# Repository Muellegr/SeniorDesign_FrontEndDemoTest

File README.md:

# SeniorDesign_FrontEndDemoTest
OSU Senior Design to demonstrate a working, very low quality front end for an oscilloscope.  
The focus of this is to test a basic fully differential op amp and applying a DC offset to the output.  
* Selectable AC or DC mode
* 5 different attenuation amounts from 1x to 20x
* Impedance matchedish to 50ohm
* Adjustable DC offset for testing from -5v to +5v
-------

Due to being used in a presentation assignment I put a lot of focus on cleary seperating system blocks at the cost of longer signal traces and effeciant layouts.  
A 4 layer board was chosen for ease of life and some signal quality. The back plane is nearly unused excluding some very minor power routing below the differential op amp.

[ Bill of Materials! ]( https://github.com/Muellegr/SeniorDesign_FrontEndDemoTest/wiki )

Schematic and all PCB layers can be found in the Schematics folder.  
* [ Schematic ]( https://raw.githubusercontent.com/Muellegr/SeniorDesign_FrontEndDemoTest/main/Front_End_Kicad/Schematics/Front_End_Kicad.pdf )
* [ Signals - Layer 1 ]( https://raw.githubusercontent.com/Muellegr/SeniorDesign_FrontEndDemoTest/main/Front_End_Kicad/Schematics/Front_End_Kicad-F_Cu.pdf )
* [ GND Plane - Layer 2]( https://raw.githubusercontent.com/Muellegr/SeniorDesign_FrontEndDemoTest/main/Front_End_Kicad/Schematics/Front_End_Kicad-in1_Cu.pdf )

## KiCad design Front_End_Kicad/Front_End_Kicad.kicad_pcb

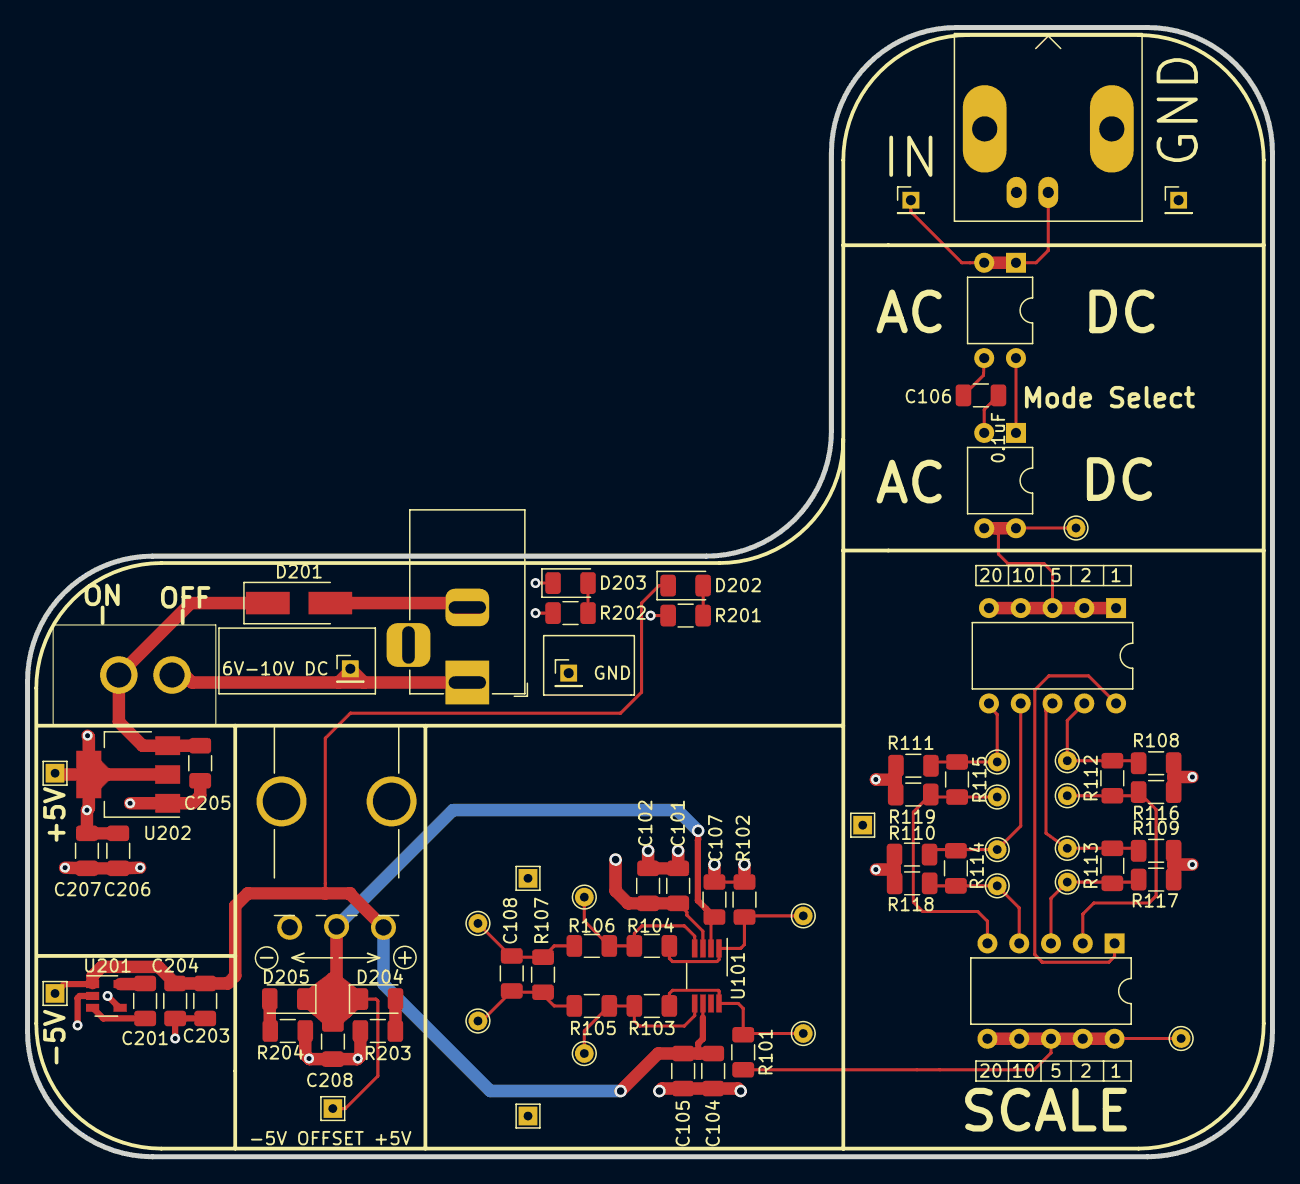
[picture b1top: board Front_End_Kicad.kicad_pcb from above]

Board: 4 copper layers, 99.5 x 90.2 mm, 79 parts (0 on the bottom side), 33 nets.

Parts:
C101, C104, C201, C203, C205, C206, C207, C208: 10uF; C_1206_3216Metric
C102, C105, C106, C107, C204: 0.1uF; C_1206_3216Metric
C108: 10pF; C_1206_3216Metric
D201: D_Zener; D_SMA_Handsoldering
D202, D203, D204, D205: LED; D_1206_3216Metric
J101: Barrel_Jack; BNC_Amphenol_B6252HB-NPP3G-50_Horizontal
J102, J103, J201, J203: Conn_01x01_Male; PinHeader_1x01_P2.00mm_Vertical
J202: Barrel_Jack; BarrelJack_Horizontal
R101, R102, R103, R104: 365; R_1206_3216Metric
R105, R106, R110, R118: 60.4; R_1206_3216Metric
R107, R115: 499; R_1206_3216Metric
R108, R116: 150; R_1206_3216Metric
R109, R117: 75; R_1206_3216Metric
R111, R119: 54.9; R_1206_3216Metric
R112: 37.4; R_1206_3216Metric
R113: 120; R_1206_3216Metric
R114: 249; R_1206_3216Metric
R201, R203, R204: 1000; R_1206_3216Metric
R202: 560; R_1206_3216Metric
RV201: R_POT; Senior_Design_Front_End
SW101, SW102: SW_DIP_x02; DIP-4_W7.62mm
SW103, SW104: SW_DIP_x05; DIP-10_W7.62mm
SW201: SW_DIP_x01; front_end_power_toggle
TP101: signal_mode_selected; TestPoint_THTPad_D1.5mm_Drill0.7mm
TP102: buffer_in+; TestPoint_THTPad_D1.5mm_Drill0.7mm
TP103: buffer_in-; TestPoint_THTPad_D1.5mm_Drill0.7mm
TP104: buffer_diff-_raw; TestPoint_THTPad_D1.5mm_Drill0.7mm
TP105: buffer_diff+_raw; TestPoint_THTPad_D1.5mm_Drill0.7mm
TP106: buff_diff_raw_gnd; TestPoint_THTPad_1.5x1.5mm_Drill0.7mm
TP107: buffer_diff-_load; TestPoint_THTPad_D1.5mm_Drill0.7mm
TP108: buffer_diff+_load; TestPoint_THTPad_D1.5mm_Drill0.7mm
TP109: buffer_diff_load_gnd; TestPoint_THTPad_1.5x1.5mm_Drill0.7mm
TP110: signal_attn; TestPoint_THTPad_D1.5mm_Drill0.7mm
TP111: attn_2x_in; TestPoint_THTPad_D1.5mm_Drill0.7mm
TP112: attn_5x_in; TestPoint_THTPad_D1.5mm_Drill0.7mm
TP113: attn_10x_in; TestPoint_THTPad_D1.5mm_Drill0.7mm
TP114: attn_20x_in; TestPoint_THTPad_D1.5mm_Drill0.7mm
TP115: attn_2x_out; TestPoint_THTPad_D1.5mm_Drill0.7mm
TP116: attn_2x_gnd; TestPoint_THTPad_1.5x1.5mm_Drill0.7mm
TP117: attn_5x_out; TestPoint_THTPad_D1.5mm_Drill0.7mm
TP119: attn_10x_out; TestPoint_THTPad_D1.5mm_Drill0.7mm
TP121: attn_20x_out; TestPoint_THTPad_D1.5mm_Drill0.7mm
TP201: v_-5v; TestPoint_THTPad_1.5x1.5mm_Drill0.7mm
TP202: v_+5v; TestPoint_THTPad_1.5x1.5mm_Drill0.7mm
TP203: v_offset; TestPoint_THTPad_1.5x1.5mm_Drill0.7mm
U101: LMH6551MM; VSSOP-8_3.0x3.0mm_P0.65mm
U201: MAX871; SOT-23-5
U202: AZ1117IH-5.0TRG1; SOT-223-3_TabPin2

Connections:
GND: C101.1, C102.1, C104.2, C105.2, C107.2, C203.1, C204.2, C205.1, C206.1, C207.2, C208.2, D201.2, D203.1, J101.2, J103.1, J201.1, J202.2, R102.1, R108.2, R109.2, R110.2, R111.2, R116.1, R117.1, R118.1, R119.1, R201.2, R203.2, R204.1, TP106.1, TP109.1, TP116.1, U201.4, U202.1
unnamed: C106.1, SW102.2
unnamed: C106.2, SW101.3
unnamed: C201.1, U201.3
unnamed: C201.2, U201.5
unnamed: D202.2, R201.1
unnamed: D203.2, R202.1
unnamed: D204.2, R203.1
unnamed: D205.2, R204.2
unnamed: J202.1, J203.1, SW201.1
unnamed: R101.1, R103.2, TP102.1, U101.8
unnamed: R102.2, R104.1, TP103.1, U101.1
unnamed: R103.1, R105.2, TP104.1, U101.5
unnamed: R104.2, R106.1, TP105.1, U101.4
unnamed: SW101.4, SW102.1
V_+5v: C101.2, C102.2, C206.2, C207.1, R202.2, RV201.3, TP202.1, U101.3, U201.2, U202.2
V_-5v: C104.1, C105.1, C203.2, C204.1, D202.1, RV201.1, TP201.1, U101.6, U201.1
V_OFFSET: C107.1, C208.1, D204.1, D205.1, RV201.2, TP203.1, U101.2
V_SUPPLY_IN: C205.2, D201.1, SW201.2, U202.3
attenuation_1x_in: SW103.10, SW104.1
attenuation_2x_in: R108.1, R112.2, SW103.9, TP111.1
attenuation_2x_out: R112.1, R116.2, SW104.2, TP115.1
attenuation_5x_in: R109.1, R113.2, SW103.8, TP112.1
attenuation_5x_out: R113.1, R117.2, SW104.3, TP117.1
attenuation_10x_in: R110.1, R114.2, SW103.7, TP113.1
attenuation_10x_out: R114.1, R118.2, SW104.4, TP119.1
attenuation_20x_in: R111.1, R115.2, SW103.6, TP114.1
attenuation_20x_out: R115.1, R119.2, SW104.5, TP121.1
buffer_v+: C108.2, R106.2, R107.2, TP108.1
buffer_v-: C108.1, R105.1, R107.1, TP107.1
signal_attenuated: R101.2, SW104.6, SW104.7, SW104.8, SW104.9, SW104.10, TP110.1
signal_mode_selected: SW102.3, SW102.4, SW103.1, SW103.2, SW103.3, SW103.4, SW103.5, TP101.1
signal_raw: J101.1, J102.1, SW101.1, SW101.2

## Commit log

2020-10-27 Inital project setup with BoM included.
2020-11-17 Some work here and there. Opamp selected and 1 voltage driver selected.
2020-11-20 Split powre system off. Small devolopment with notes and layout.
2020-11-20 Added footprints and digikey links to many of the components. Missing is the primary amplifier
2020-11-21 All parts designed in schematic and preparing to enter PCB design
2020-11-21 Started work on PCB. Sections seperated and partially connected. Planning 4 layer
2020-11-22 PCB nearly complete. Added schematics and layers
2020-11-22 Added names to parts to show better
2020-11-22 Resized image
2020-11-22 Revised PCB picure
2020-11-22 Added pictures
2020-11-22 Update README.md
    Added pretty pictures
2020-11-25 Updated schematic
